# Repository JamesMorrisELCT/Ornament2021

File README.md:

# Ornament2021
Snowflake Ornament Files
Created December 2021 by James Morris

This project is a work in progress at the moment

In this Github directory, you will find the files used to design the PCB, the circuit diagrams, the Bill of Materials, and the arduino code that was used to design the ornament

In order to view the PCB files or the circuit diagram, you will need to have KiCad v5.0+ installed, and then download the project file found under "KiCad Files"

In order to make changes to the arduino code to customiza the lighting sequence of your ornament, you will need to do the following

1. TODO: add instructions on how to upload to lilypad arduino

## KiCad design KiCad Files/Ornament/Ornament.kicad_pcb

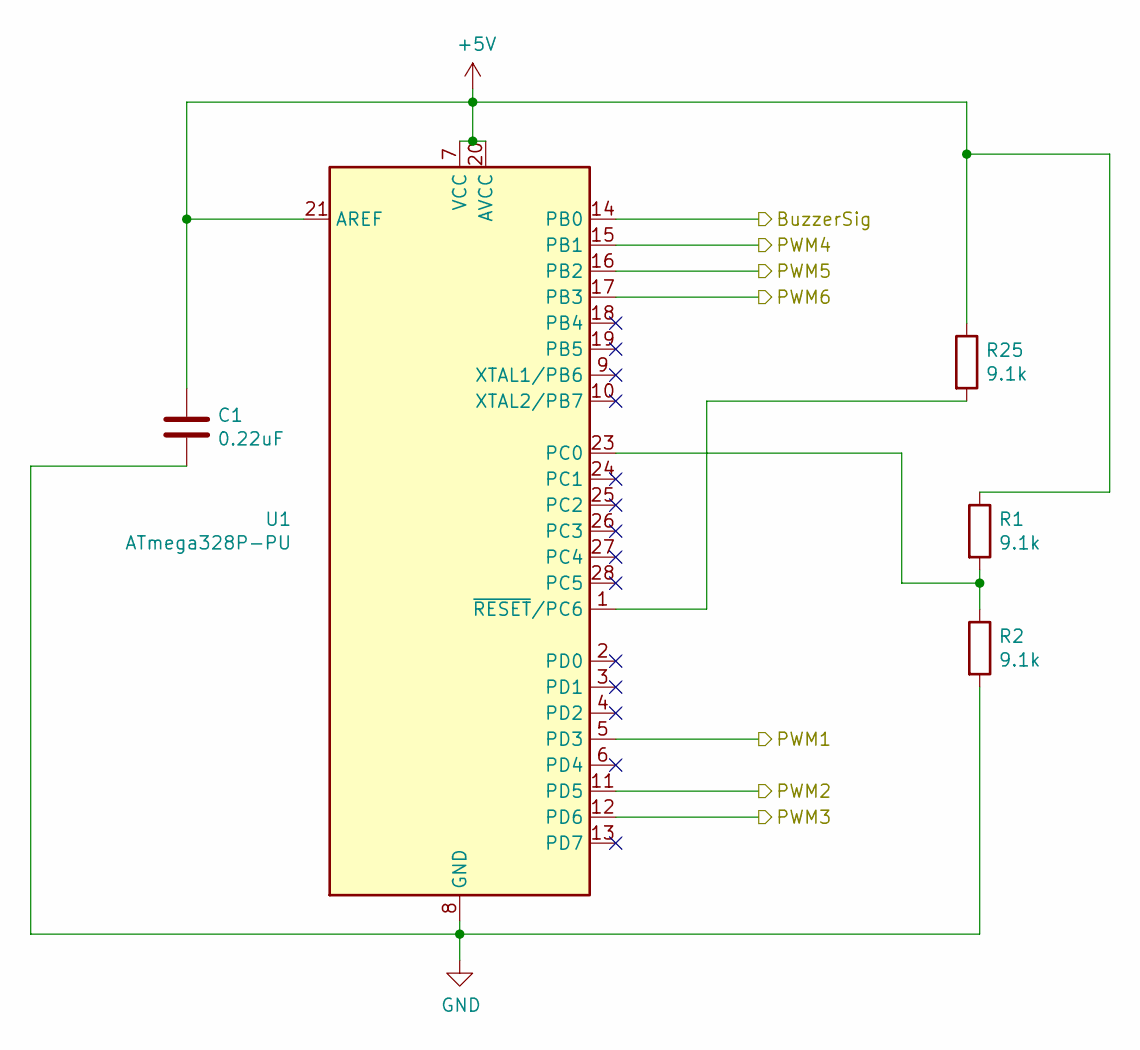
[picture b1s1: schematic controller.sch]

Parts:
C1: 0.22uF; C_1206_3216Metric_Pad1.33x1.80mm_HandSolder
R1, R2, R25: 9.1k; R_1206_3216Metric_Pad1.30x1.75mm_HandSolder
U1: ATmega328P-PU; DIP-28_W7.62mm_Socket

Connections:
+5V: C1.1, R1.1, R25.1, U1.7 (VCC), U1.20 (AVCC), U1.21 (AREF); also elsewhere on the board
/LED Schematic/Branch1On: U1.5 (PD3); also elsewhere on the board
/LED Schematic/Branch2On: U1.11 (PD5); also elsewhere on the board
/LED Schematic/Branch3On: U1.12 (PD6); also elsewhere on the board
/LED Schematic/Branch4On: U1.15 (PB1); also elsewhere on the board
/LED Schematic/Branch5On: U1.16 (PB2); also elsewhere on the board
/LED Schematic/Branch6On: U1.17 (PB3)
/Power + Other/Buzzer: U1.14 (PB0); also elsewhere on the board
GND: C1.2, R2.2, U1.8 (GND), U1.22 (GND); also elsewhere on the board
unnamed: R1.2, R2.1, U1.23 (PC0)
unnamed: R25.2, U1.1 (~RESET~/PC6)

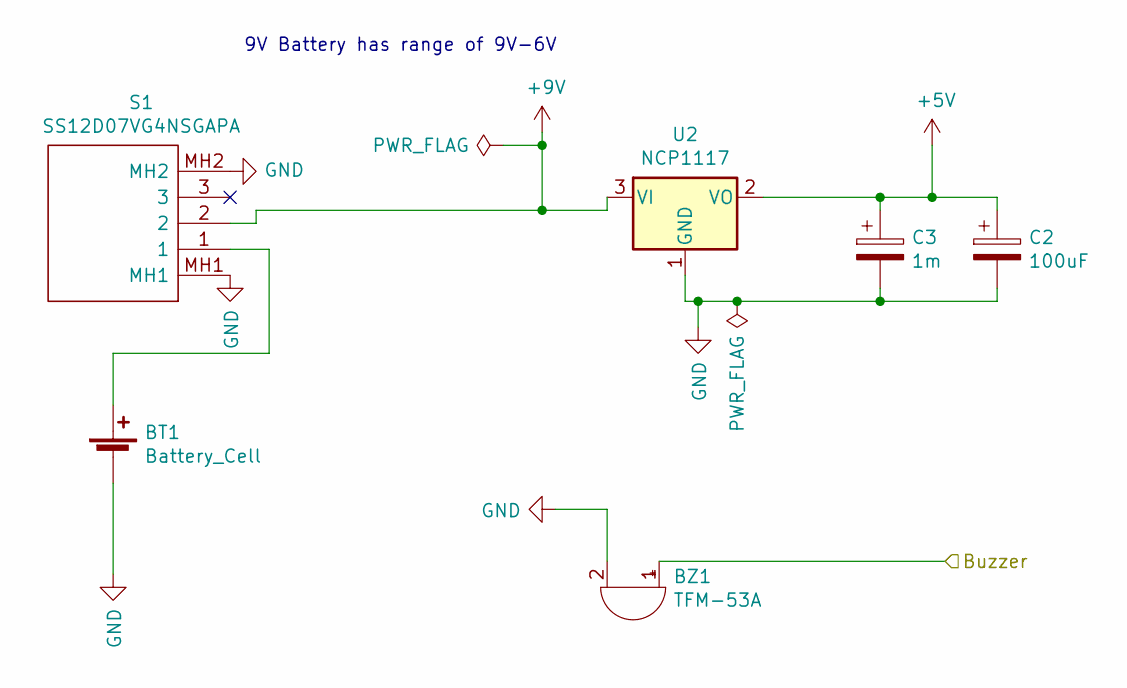
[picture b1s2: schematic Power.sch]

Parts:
BT1: Battery_Cell; Battery_9V_Connections_Seperate
BZ1: TFM-53A; R_Bare_Metal_Element_L16.3mm_W4.8mm_P15.30mm
C2: 100uF; CP_Radial_D5.0mm_P2.00mm
C3: 1m; C_Radial_D8.0mm_H11.5mm_P3.50mm
S1: SS12D07VG4NSGAPA; Mouser Part Number 611-SS12D07VG4NSGAPA
U2: NCP1117; TO-252-2

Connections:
+5V: C2.1, C3.1, U2.2 (VO); also elsewhere on the board
+9V: S1.2, U2.3 (VI)
/Power + Other/Buzzer: BZ1.1 (-); also elsewhere on the board
GND: BT1.2 (-), BZ1.2 (+), C2.2, C3.2, S1.MH1, S1.MH2, U2.1 (GND); also elsewhere on the board
unnamed: BT1.1 (+), S1.1

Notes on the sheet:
9V Battery has range of 9V-6V

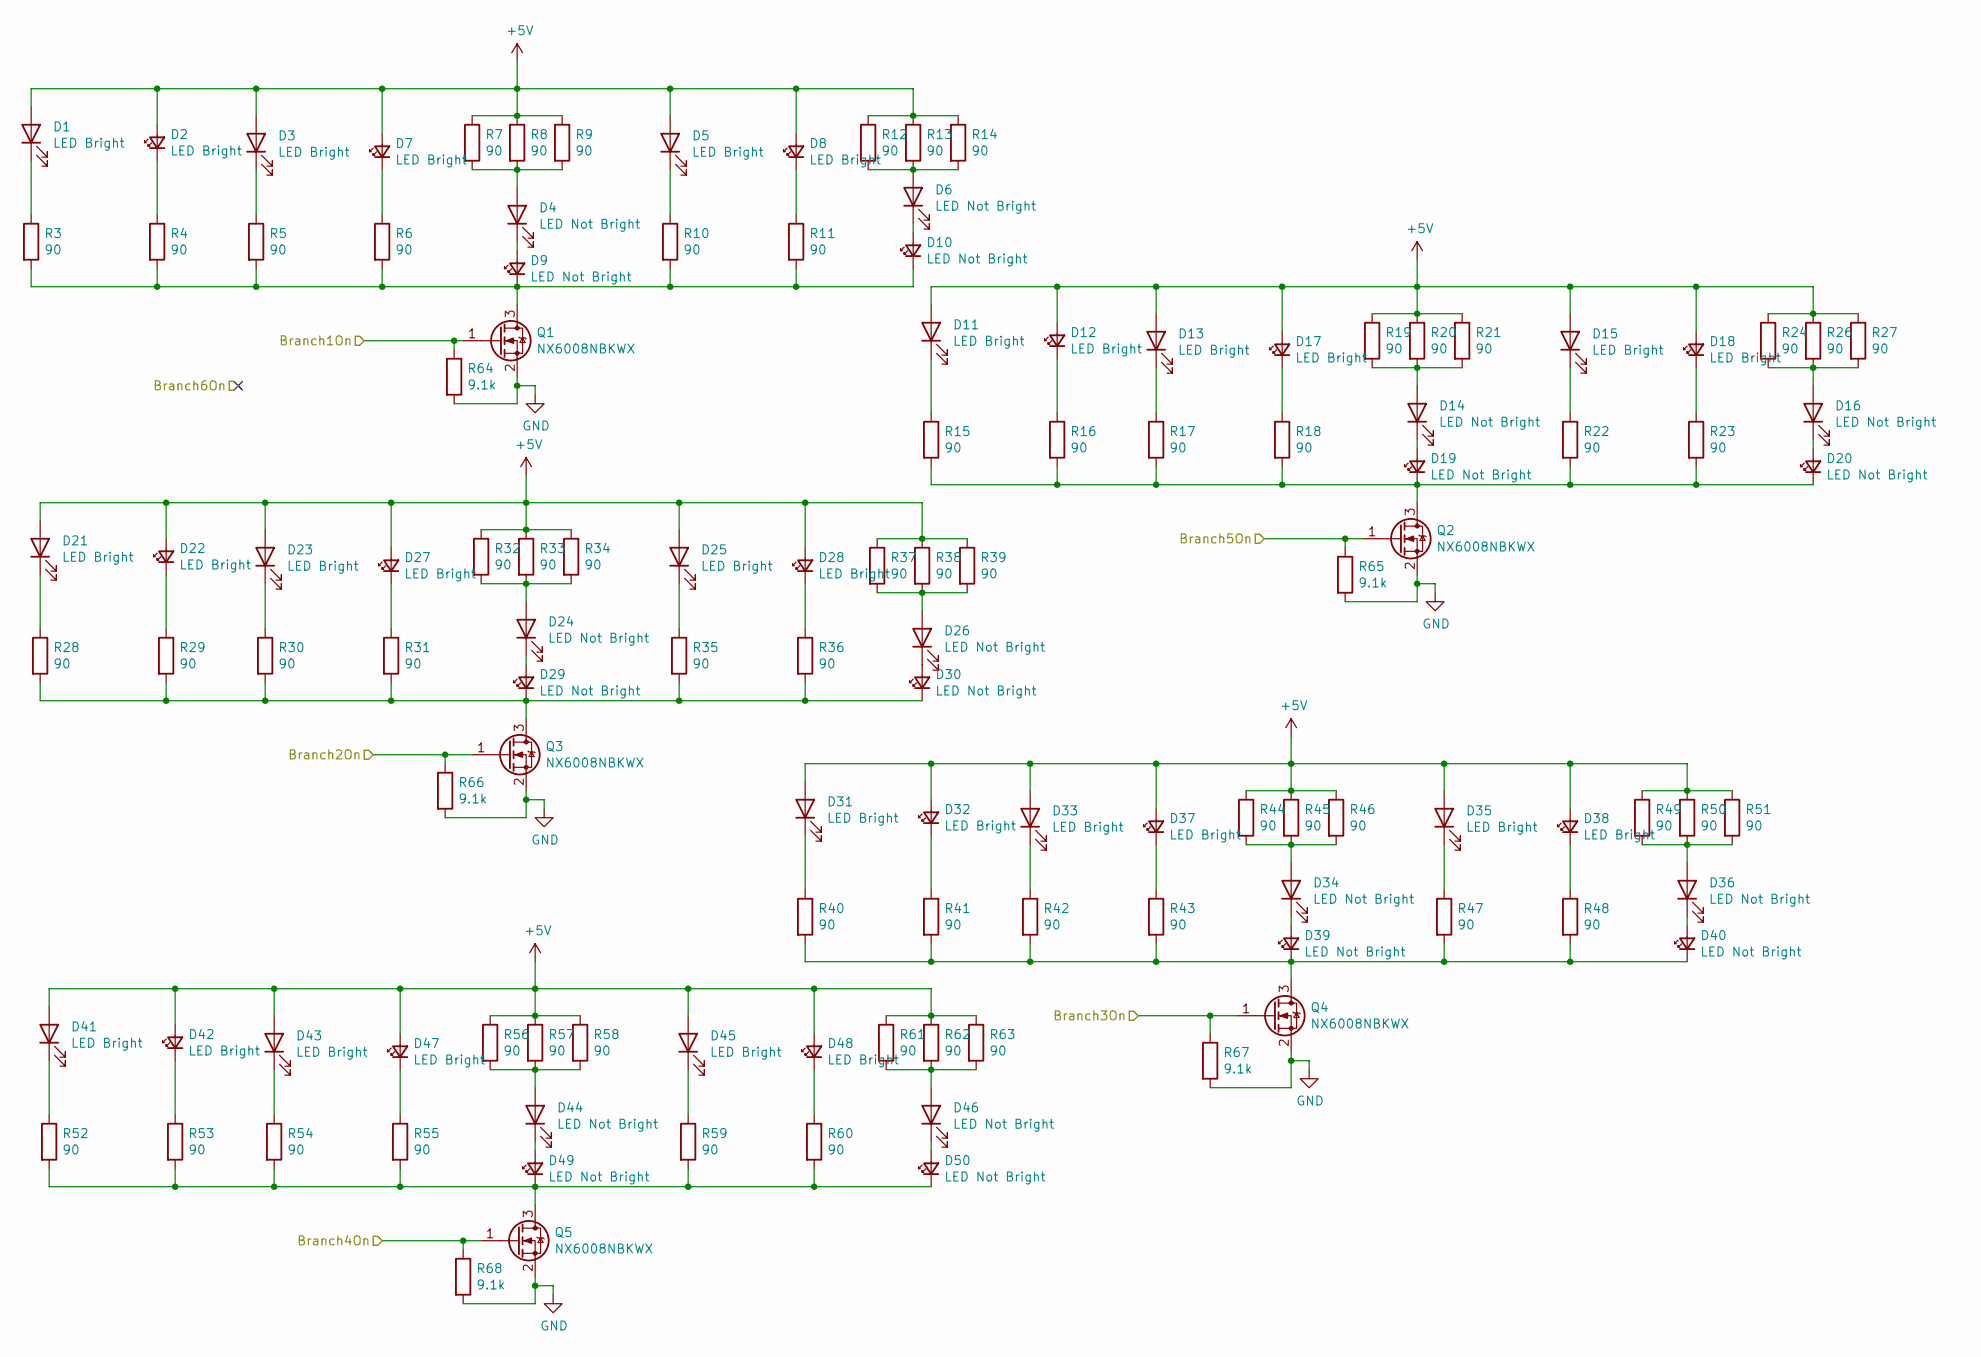
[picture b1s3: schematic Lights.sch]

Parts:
D1, D3, D5, D11, D13, D15, D21, D23, D25, D31, D33, D35, D41, D43, D45: LED Bright; LED_D5.0mm
D2, D7, D8, D12, D17, D18, D22, D27, D28, D32, D37, D38, D42, D47, D48: LED Bright; LED_1206_3216Metric_Pad1.42x1.75mm_HandSolder
D4, D6, D14, D16, D24, D26, D34, D36, D44, D46: LED Not Bright; LED_D5.0mm
D9, D10, D19, D20, D29, D30, D39, D40, D49, D50: LED Not Bright; LED_1206_3216Metric_Pad1.42x1.75mm_HandSolder
Q1, Q2, Q3, Q4, Q5: NX6008NBKWX; SOT-323_SC-70_Handsoldering
R3, R4, R5, R6, R7, R8, R9, R10, R11, R12, R13, R14, R15, R16, R17, R18, R19, R20, R21, R22, R23, R24, R26, R27, R28, R29, R30, R31, R32, R33, R34, R35, R36, R37, R38, R39, R40, R41, R42, R43, R44, R45, R46, R47, R48, R49, R50, R51, R52, R53, R54, R55, R56, R57, R58, R59, R60, R61, R62, R63: 90; R_1206_3216Metric_Pad1.30x1.75mm_HandSolder
R64, R65, R66, R67, R68: 9.1k; R_1206_3216Metric_Pad1.30x1.75mm_HandSolder

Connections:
+5V: D1.2 (A), D2.2 (A), D3.2 (A), D5.2 (A), D7.2 (A), D8.2 (A), D11.2 (A), D12.2 (A), D13.2 (A), D15.2 (A), D17.2 (A), D18.2 (A), D21.2 (A), D22.2 (A), D23.2 (A), D25.2 (A), D27.2 (A), D28.2 (A), D31.2 (A), D32.2 (A), D33.2 (A), D35.2 (A), D37.2 (A), D38.2 (A), D41.2 (A), D42.2 (A), D43.2 (A), D45.2 (A), D47.2 (A), D48.2 (A), R7.1, R8.1, R9.1, R12.1, R13.1, R14.1, R19.1, R20.1, R21.1, R24.1, R26.1, R27.1, R32.1, R33.1, R34.1, R37.1, R38.1, R39.1, R44.1, R45.1, R46.1, R49.1, R50.1, R51.1, R56.1, R57.1, R58.1, R61.1, R62.1, R63.1; also elsewhere on the board
/LED Schematic/Branch1On: Q1.1 (G), R64.1; also elsewhere on the board
/LED Schematic/Branch2On: Q3.1 (G), R66.1; also elsewhere on the board
/LED Schematic/Branch3On: Q4.1 (G), R67.1; also elsewhere on the board
/LED Schematic/Branch4On: Q5.1 (G), R68.1; also elsewhere on the board
/LED Schematic/Branch5On: Q2.1 (G), R65.1; also elsewhere on the board
GND: Q1.2 (S), Q2.2 (S), Q3.2 (S), Q4.2 (S), Q5.2 (S), R64.2, R65.2, R66.2, R67.2, R68.2; also elsewhere on the board
unnamed: D1.1 (K), R3.1
unnamed: D2.1 (K), R4.1
unnamed: D3.1 (K), R5.1
unnamed: D4.1 (K), D9.2 (A)
unnamed: D4.2 (A), R7.2, R8.2, R9.2
unnamed: D5.1 (K), R10.1
unnamed: D6.2 (A), R12.2, R13.2, R14.2
unnamed: D7.1 (K), R6.1
unnamed: D8.1 (K), R11.1
unnamed: D9.1 (K), D10.1 (K), Q1.3 (D), R3.2, R4.2, R5.2, R6.2, R10.2, R11.2
unnamed: D6.1 (K), D10.2 (A)
unnamed: D11.1 (K), R15.1
unnamed: D12.1 (K), R16.1
unnamed: D13.1 (K), R17.1
unnamed: D14.1 (K), D19.2 (A)
unnamed: D14.2 (A), R19.2, R20.2, R21.2
unnamed: D15.1 (K), R22.1
unnamed: D16.1 (K), D20.2 (A)
unnamed: D16.2 (A), R24.2, R26.2, R27.2
unnamed: D17.1 (K), R18.1
unnamed: D18.1 (K), R23.1
unnamed: D19.1 (K), D20.1 (K), Q2.3 (D), R15.2, R16.2, R17.2, R18.2, R22.2, R23.2
unnamed: D21.1 (K), R28.1
unnamed: D22.1 (K), R29.1
unnamed: D23.1 (K), R30.1
unnamed: D24.1 (K), D29.2 (A)
unnamed: D24.2 (A), R32.2, R33.2, R34.2
unnamed: D25.1 (K), R35.1
unnamed: D26.1 (K), D30.2 (A)
unnamed: D26.2 (A), R37.2, R38.2, R39.2
unnamed: D27.1 (K), R31.1
unnamed: D28.1 (K), R36.1
unnamed: D29.1 (K), D30.1 (K), Q3.3 (D), R28.2, R29.2, R30.2, R31.2, R35.2, R36.2
unnamed: D31.1 (K), R40.1
unnamed: D32.1 (K), R41.1
unnamed: D33.1 (K), R42.1
unnamed: D34.1 (K), D39.2 (A)
unnamed: D34.2 (A), R44.2, R45.2, R46.2
unnamed: D35.1 (K), R47.1
unnamed: D36.1 (K), D40.2 (A)
unnamed: D36.2 (A), R49.2, R50.2, R51.2
unnamed: D37.1 (K), R43.1
unnamed: D38.1 (K), R48.1
unnamed: D39.1 (K), D40.1 (K), Q4.3 (D), R40.2, R41.2, R42.2, R43.2, R47.2, R48.2
unnamed: D41.1 (K), R52.1
unnamed: D42.1 (K), R53.1
unnamed: D43.1 (K), R54.1
unnamed: D44.1 (K), D49.2 (A)
unnamed: D44.2 (A), R56.2, R57.2, R58.2
unnamed: D45.1 (K), R59.1
unnamed: D46.1 (K), D50.2 (A)
unnamed: D46.2 (A), R61.2, R62.2, R63.2
unnamed: D47.1 (K), R55.1
unnamed: D48.1 (K), R60.1
unnamed: D49.1 (K), D50.1 (K), Q5.3 (D), R52.2, R53.2, R54.2, R55.2, R59.2, R60.2

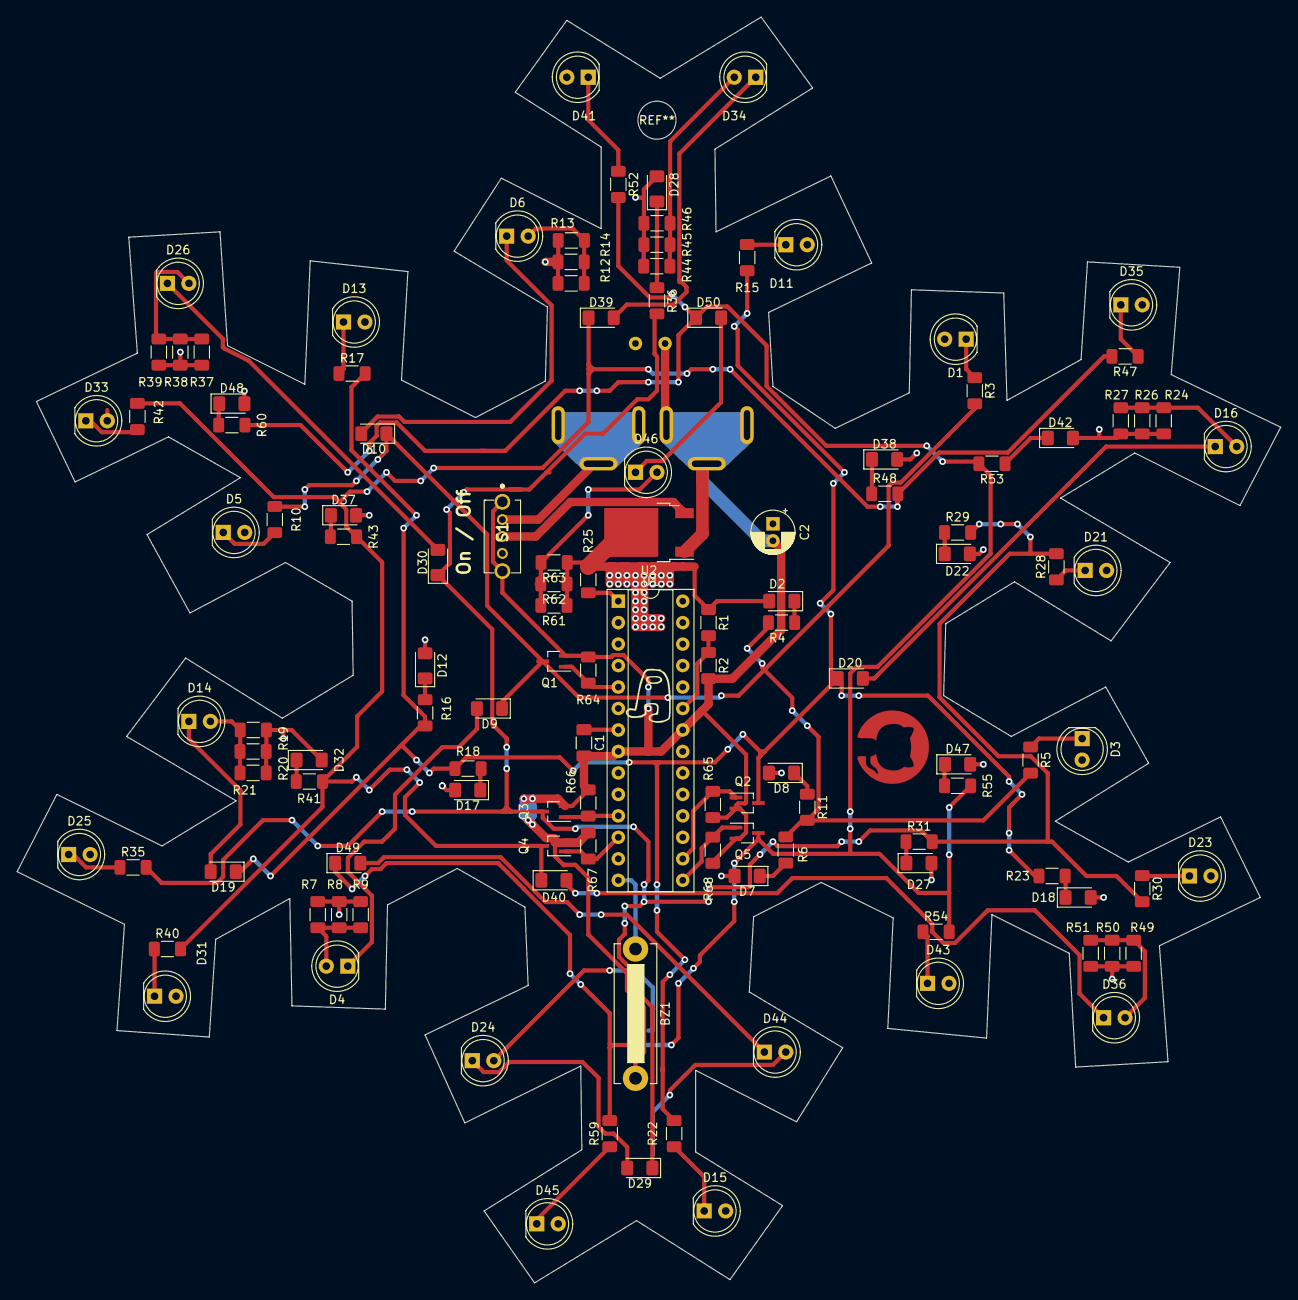
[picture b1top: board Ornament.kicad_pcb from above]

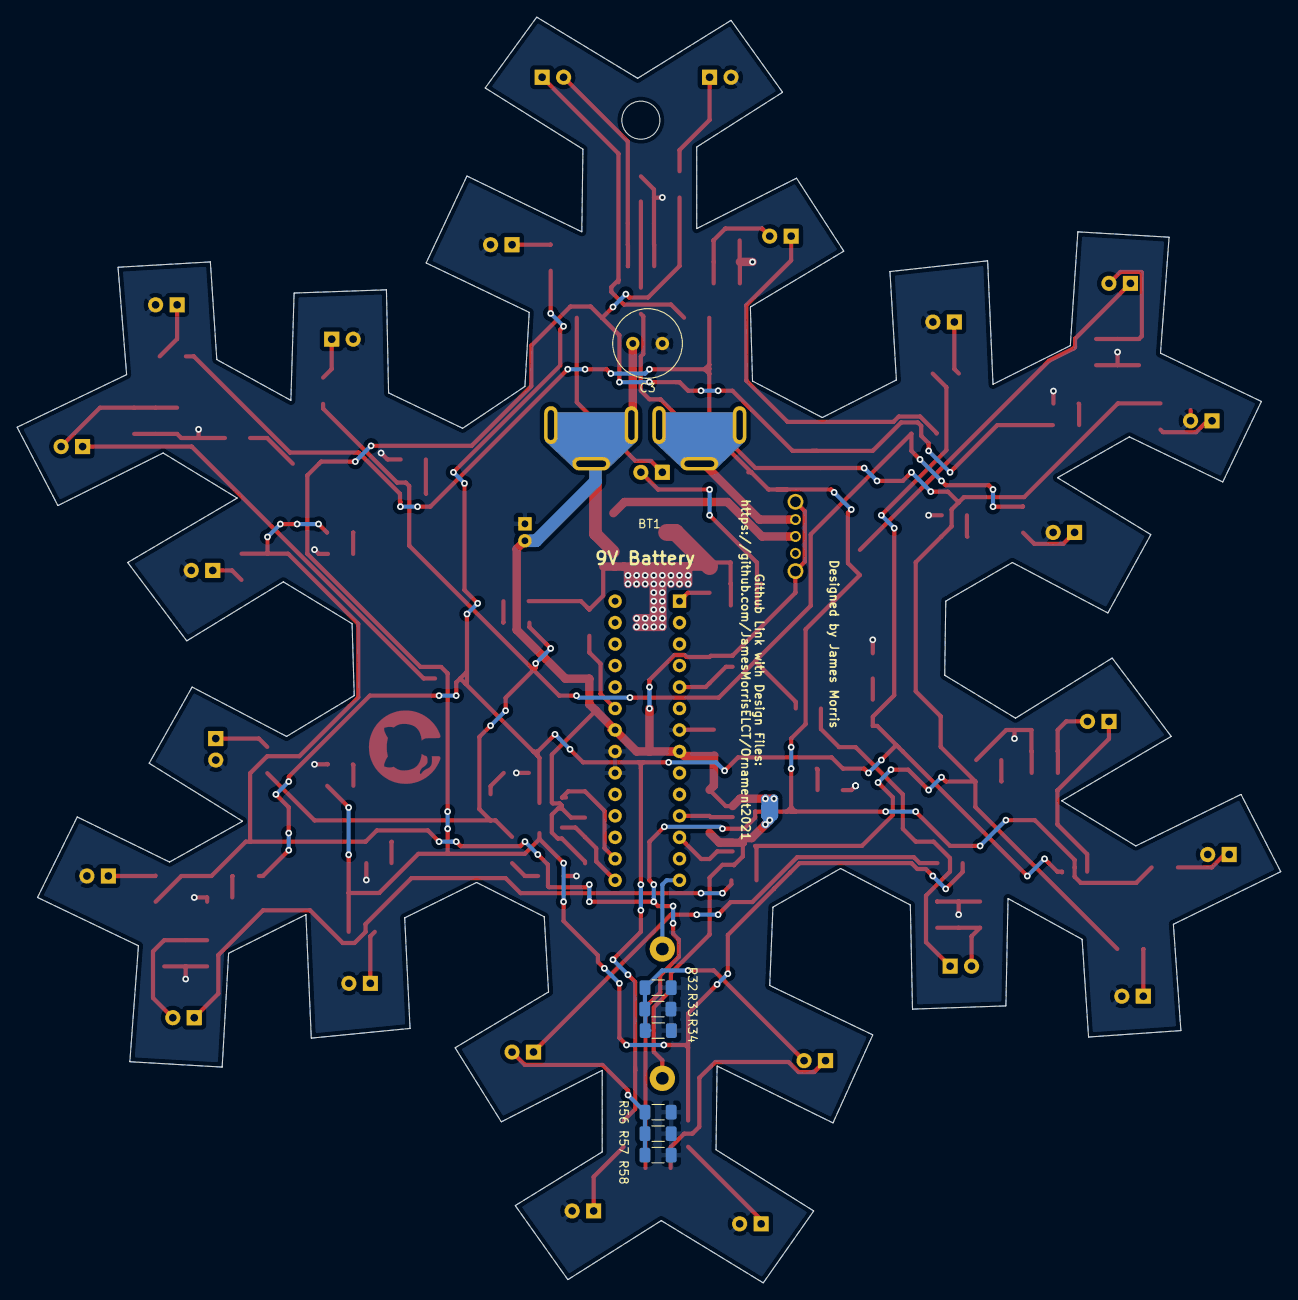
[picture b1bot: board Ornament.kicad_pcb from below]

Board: 2 copper layers, 149.5 x 149.7 mm, 131 parts (8 on the bottom side), 67 nets.

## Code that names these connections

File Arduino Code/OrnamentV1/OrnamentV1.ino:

/*      Christmas Ornament v1
 *      Code constructed by James Morris - December 2021
 *      All design files including PCB design and arduino code can be found at https://github.com/JamesMorrisELCT/Ornament2021
 *      This code is as it was distrubuted on the ornaments
 */


//Creating references for the output control registers so that the code is easier to understand, each one controls the PWM of a single channel
volatile uint8_t& section1 = OCR0A;
volatile uint8_t& section2 = OCR0B;
volatile uint16_t& section3 = OCR1A;
volatile uint16_t& section4 = OCR1B;
volatile uint8_t& section5 = OCR2B;
//volatile uint8_t& section6 = OCR2A;

//OnValue changes the maximum brightness of the LEDs
int onValue = 10; // Maximum value of PWM  maximum possible is 255, minimum is 1

uint8_t mode;  //Mode of lighting
               // Only a single mode has been included with v1

int delayTime=100;  //Time in arbitrary unit (dependent on Clock speed) that is referenced for the blinking timing (make lower for faster, larger for slower)

void setup() {

  //TODO: Add support for a pushbutton that switched modes

  //Setting the pins as outputs
  pinMode(PD6, OUTPUT);   //OC0A
  pinMode(PD5, OUTPUT);   //OC0B
  pinMode(PB1, OUTPUT);   //OC1A
  pinMode(PB2, OUTPUT);   //OC1B
  pinMode(PD3, OUTPUT);   //OC2B
  //pinMode(PB3, OUTPUT); //OC2A UNUSED ATM

  setupPWM();
  findTurnOnValue();

  mode=0;

}

void loop() {
  if(mode==0){
    //Simple routine that just turns on each channel for a set time one at a time
    turnOn(section1);
    delay(delayTime);
    allOff();
    turnOn(section2);
    delay(delayTime);
    allOff();
    turnOn(section3);
    //section3=onValue;
    delay(delayTime);
    allOff();
    turnOn(section4);
    //section4=onValue;
    delay(delayTime);
    allOff();
    turnOn(section5);
    delay(delayTime);
    allOff();
  } else {
    allOff();
  }
}


void turnOn(volatile uint8_t& reg){ //Turns on a specific channel
  reg=onValue;
}

void turnOn(volatile uint16_t& reg){ //Turns on a specific channel
  reg=onValue;
}

void turnOff(volatile uint8_t& reg){  //Turns off a specific channel
  reg=0;
}

void turnOff(volatile uint16_t& reg){  //Turns off a specific channel
  reg=0;
}

void allOff() { //Turns all the channels off
  section1=0;
  section2=0;
  section3=0;
  section4=0;
  section5=0;
}

void setupPWM(){ //Sets up the Timer0 Timer1 and Timer2 registers to support the 8 bit fast PWM mode on each
  TCCR0A = _BV(COM0A1) | _BV(COM0B1) | _BV(WGM21) | _BV(WGM20);
  TCCR0B = _BV(CS22);
  TCCR2A = _BV(COM2A1) | _BV(COM2B1) | _BV(WGM21) | _BV(WGM20);
  TCCR2B = _BV(CS22);

  TCCR1A = (1<<COM1A1) + (1<<COM1B1) + (1<<WGM10); //non inverting A and B outputs, mode 5 (fast pwm 8 bit)
  TCCR1B = (1<<WGM12) + (1<<CS12); // prescaler = 256
  DDRB |= (1<<PB1)|(1<<PB2);

  allOff();
}

void testFCLK(volatile uint8_t& reg){ //OBSOLETE
  noInterrupts();
  reg = _BV(CLKPCE); // 0x80
  reg = _BV(CLKPS3); // 0x03
  interrupts();
}

void findTurnOnValue(){
  //TODO change on value depending on number of times power has been cycled using EEPROM
  onValue=10;
}
